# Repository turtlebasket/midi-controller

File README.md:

# Pocket Operator

## Contents

- [`device`](device/) - Board design files ([see README](device/README.md))
- [`firmware`](firmware/) - Device firmware ([see README](firmware/README.md))

## Gallery

| Completed Board (bird's eye) | Completed Board (top) |
| --------------- | -------- |
|  |  | 

| Layout (Top) | Layout (Bottom) | Layout (Full) |
| ------------ | --------------- | ------------- |
|  |  |  |

| Schematic |
| --------- |

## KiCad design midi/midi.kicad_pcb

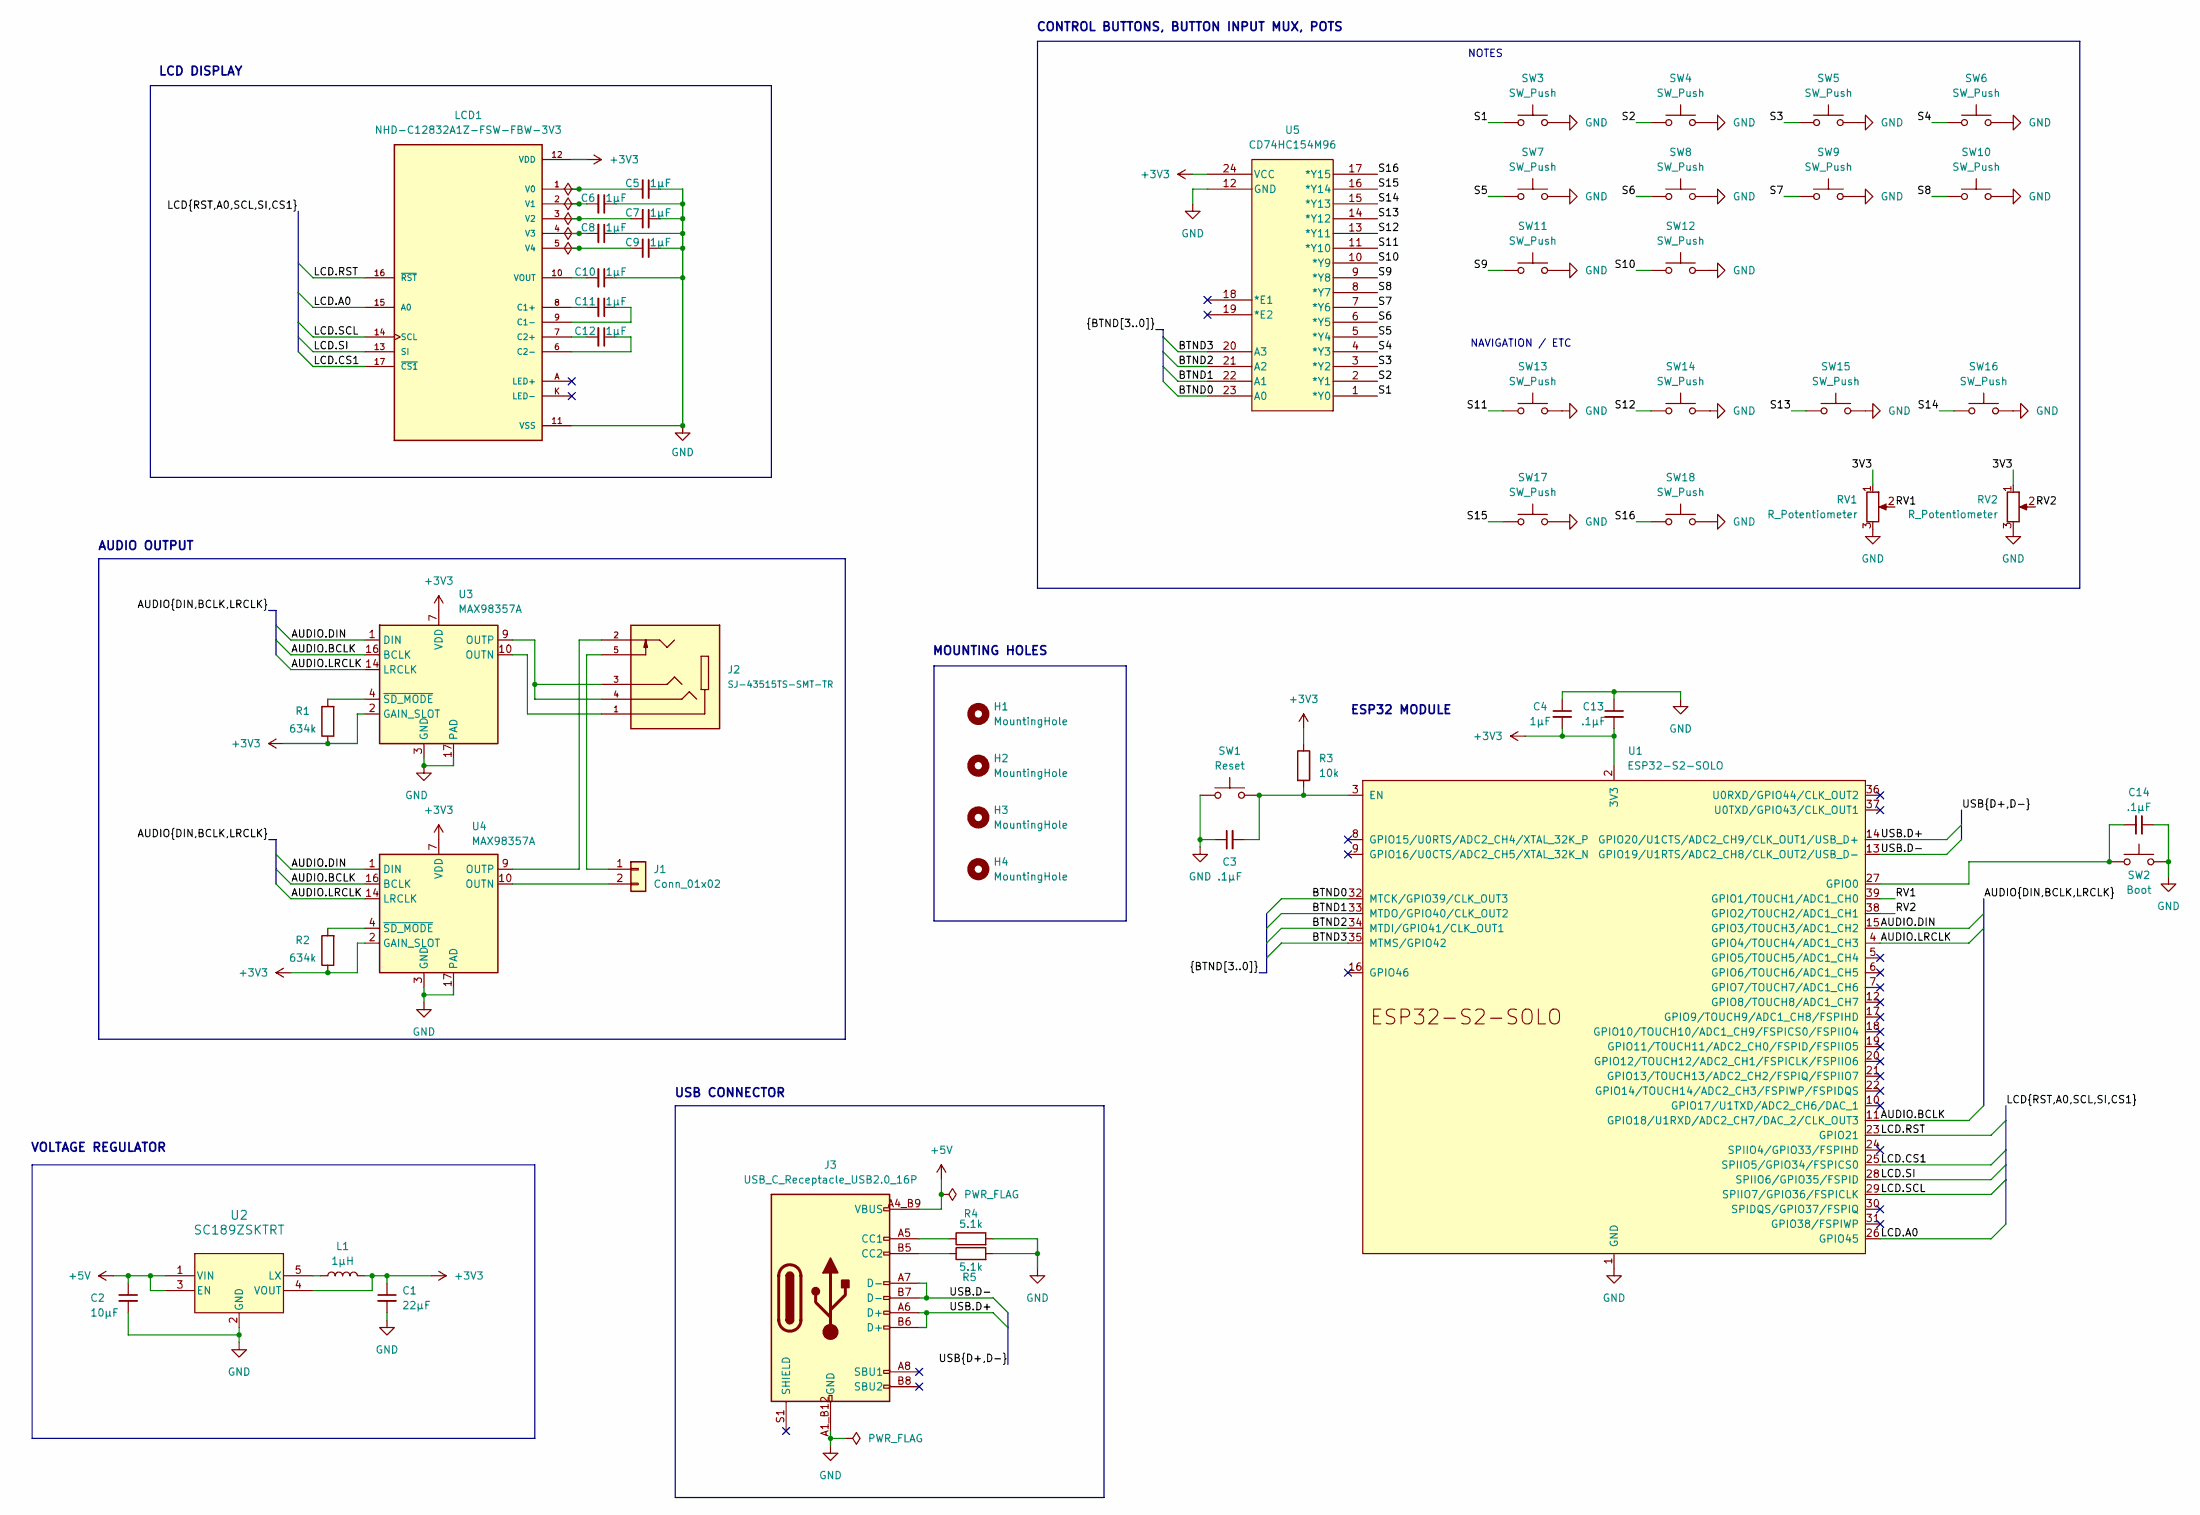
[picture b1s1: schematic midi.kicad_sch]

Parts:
C1: 22µF; C_0603_1608Metric_Pad1.08x0.95mm_HandSolder
C2: 10µF; C_0603_1608Metric_Pad1.08x0.95mm_HandSolder
C3, C13, C14: .1µF; C_0603_1608Metric_Pad1.08x0.95mm_HandSolder
C4: 1µF; C_0603_1608Metric_Pad1.08x0.95mm_HandSolder
C5, C6, C7, C8, C9, C10, C11, C12: 1µF; C_0603_1608Metric
H1, H2, H3, H4: MountingHole; MountingHole_2.2mm_M2
J1: Conn_01x02; PinHeader_1x02_P2.54mm_Vertical
J2: SJ-43515TS-SMT-TR; CUI_SJ-43515TS-SMT-TR; PARTREV 1.05
J3: USB_C_Receptacle_USB2.0_16P; GCT_USB4105-GF-A
L1: 1µH; L_0805_2012Metric_Pad1.15x1.40mm_HandSolder
LCD1: NHD-C12832A1Z-FSW-FBW-3V3; LCD_NHD-C12832A1Z-FSW-FBW-3V3; PARTREV 7
R1, R2: 634k; R_0603_1608Metric_Pad0.98x0.95mm_HandSolder
R3: 10k; R_0603_1608Metric_Pad0.98x0.95mm_HandSolder
R4, R5: 5.1k; R_0805_2012Metric_Pad1.20x1.40mm_HandSolder
RV1, RV2: R_Potentiometer; POT_PRS11R-4-S_BRN
SW1: Reset; SW_PUSH_6mm_H5mm
SW2: Boot; SW_PUSH_6mm_H5mm
SW3, SW4, SW5, SW6, SW7, SW8, SW9, SW10, SW11, SW12, SW13, SW14, SW15, SW16, SW17, SW18: SW_Push; SW_PUSH_6mm_H5mm
U1: ESP32-S2-SOLO
U2: SC189ZSKTRT; SOT23-5-SC189_SEM
U3, U4: MAX98357A; TQFN-16-1EP_3x3mm_P0.5mm_EP1.23x1.23mm
U5: CD74HC154M96; DW24

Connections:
+3V3: C1.1, C4.2, C13.2, L1.2, LCD1.12 (VDD), R1.1, R2.1, R3.1, U1.2 (3V3), U2.4 (VOUT), U3.2 (GAIN_SLOT), U3.7 (VDD), U3.8 (VDD), U4.2 (GAIN_SLOT), U4.7 (VDD), U4.8 (VDD), U5.24 (VCC)
+5V: C2.1, J3.A4_B9 (VBUS), J3.A9 (VBUS), J3.B4 (VBUS), J3.B9 (VBUS), U2.1 (VIN), U2.3 (EN)
/3V3: RV1.1, RV2.1
/AUDIO.BCLK: U1.11 (GPIO18/U1RXD/ADC2_CH7/DAC_2/CLK_OUT3), U3.16 (BCLK), U4.16 (BCLK)
/AUDIO.DIN: U1.15 (GPIO3/TOUCH3/ADC1_CH2), U3.1 (DIN), U4.1 (DIN)
/AUDIO.LRCLK: U1.4 (GPIO4/TOUCH4/ADC1_CH3), U3.14 (LRCLK), U4.14 (LRCLK)
/BTND0: U1.32 (MTCK/GPIO39/CLK_OUT3), U5.23 (A0)
/BTND1: U1.33 (MTDO/GPIO40/CLK_OUT2), U5.22 (A1)
/BTND2: U1.34 (MTDI/GPIO41/CLK_OUT1), U5.21 (A2)
/BTND3: U1.35 (MTMS/GPIO42), U5.20 (A3)
/LCD.A0: LCD1.15 (A0), U1.26 (GPIO45)
/LCD.CS1: LCD1.17 (~CS1), U1.25 (SPIIO5/GPIO34/FSPICS0)
/LCD.RST: LCD1.16 (~RST), U1.23 (GPIO21)
/LCD.SCL: LCD1.14 (SCL), U1.29 (SPIIO7/GPIO36/FSPICLK)
/LCD.SI: LCD1.13 (SI), U1.28 (SPIIO6/GPIO35/FSPID)
/RV1: RV1.2, U1.39 (GPIO1/TOUCH1/ADC1_CH0)
/RV2: RV2.2, U1.38 (GPIO2/TOUCH2/ADC1_CH1)
/S1: SW3.1, U5.1 (*Y0)
/S2: SW4.1, U5.2 (*Y1)
/S3: SW5.1, U5.3 (*Y2)
/S4: SW6.1, U5.4 (*Y3)
/S5: SW7.1, U5.5 (*Y4)
/S6: SW8.1, U5.6 (*Y5)
/S7: SW9.1, U5.7 (*Y6)
/S8: SW10.1, U5.8 (*Y7)
/S9: SW11.1, U5.9 (*Y8)
/S10: SW12.1, U5.10 (*Y9)
/S11: SW13.1, U5.11 (*Y10)
/S12: SW14.1, U5.13 (*Y11)
/S13: SW15.1, U5.14 (*Y12)
/S14: SW16.1, U5.15 (*Y13)
/S15: SW17.1, U5.16 (*Y14)
/S16: SW18.1, U5.17 (*Y15)
/USB.D+: J3.A6 (D+), J3.B6 (D+), U1.14 (GPIO20/U1CTS/ADC2_CH9/CLK_OUT1/USB_D+)
/USB.D-: J3.A7 (D-), J3.B7 (D-), U1.13 (GPIO19/U1RTS/ADC2_CH8/CLK_OUT2/USB_D-)
GND: C1.2, C2.2, C3.1, C4.1, C5.1, C6.1, C7.1, C8.1, C9.1, C10.1, C13.1, C14.1, J3.A1_B12 (GND), J3.A12 (GND), J3.B1 (GND), J3.B12 (GND), LCD1.11 (VSS), R4.2, R5.2, RV1.3, RV2.3, SW1.1, SW2.2, SW3.2, SW4.2, SW5.2, SW6.2, SW7.2, SW8.2, SW9.2, SW10.2, SW11.2, SW12.2, SW13.2, SW14.2, SW15.2, SW16.2, SW17.2, SW18.2, U1.1 (GND), U1.40 (GND), U1.41 (GND), U2.2 (GND), U3.3 (GND), U3.11 (GND), U3.15 (GND), U3.17 (PAD), U4.3 (GND), U4.11 (GND), U4.15 (GND), U4.17 (PAD), U5.12 (GND)
unnamed: J1.1, J2.5
unnamed: J1.2, U4.10 (OUTN)
unnamed: J3.A5 (CC1), R4.1
unnamed: J3.B5 (CC2), R5.1
unnamed: C11.2, LCD1.8 (C1+)
unnamed: C11.1, LCD1.9 (C1-)
unnamed: C12.2, LCD1.7 (C2+)
unnamed: C12.1, LCD1.6 (C2-)
unnamed: C5.2, LCD1.1 (V0)
unnamed: C6.2, LCD1.2 (V1)
unnamed: C7.2, LCD1.3 (V2)
unnamed: C8.2, LCD1.4 (V3)
unnamed: C9.2, LCD1.5 (V4)
unnamed: C10.2, LCD1.10 (VOUT)
unnamed: C3.2, R3.2, SW1.2, U1.3 (EN)
unnamed: C14.2, SW2.1, U1.27 (GPIO0)
unnamed: L1.1, U2.5 (LX)
unnamed: J2.1, U3.10 (OUTN)
unnamed: J2.3, J2.4, U3.9 (OUTP)
unnamed: R1.2, U3.4 (~SD_MODE)
unnamed: J2.2, U4.9 (OUTP)
unnamed: R2.2, U4.4 (~SD_MODE)

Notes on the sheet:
VOLTAGE REGULATOR
CONTROL BUTTONS, BUTTON INPUT MUX, POTS
AUDIO OUTPUT
MOUNTING HOLES
USB CONNECTOR
NOTES
ESP32 MODULE
NAVIGATION / ETC
LCD DISPLAY

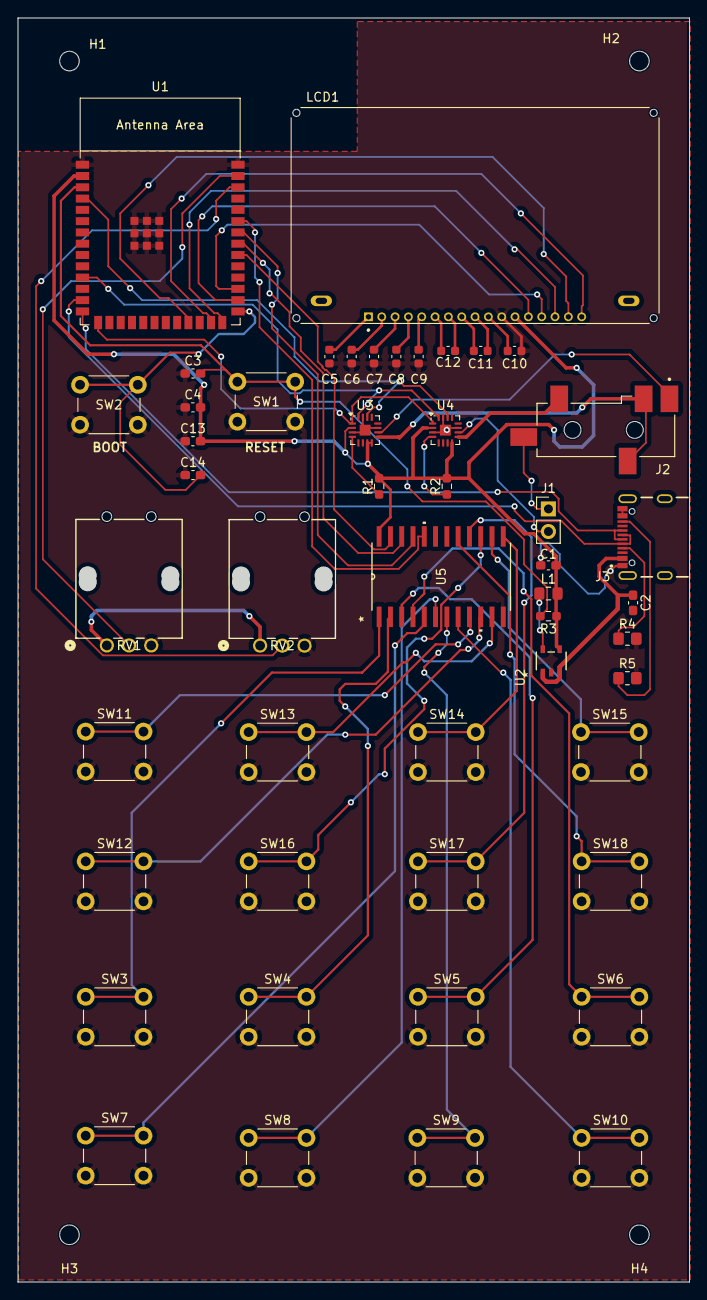
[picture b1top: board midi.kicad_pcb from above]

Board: 2 copper layers, 75.6 x 142.2 mm, 53 parts (0 on the bottom side), 58 nets.

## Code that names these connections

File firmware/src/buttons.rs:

use esp_idf_hal::{gpio::*, io::Error, peripherals::Peripherals, sys::EspError};

pub fn init_buttons() -> Result<[PinDriver<'static, AnyInputPin, Pull>; 4], EspError> {
    let peripherals = match Peripherals::take() {
        Ok(p) => p,
        Err(e) => return Err(e),
    };

    // wired to GPIO0, GPIO1, GPIO2, GPIO3
    let mut mux_bits = [
        (match PinDriver::input(peripherals.pins.gpio0) {
            Ok(b) => b,
            Err(e) => return Err(e),
        }),
        (match PinDriver::input(peripherals.pins.gpio1) {
            Ok(b) => b,
            Err(e) => return Err(e),
        }),
        (match PinDriver::input(peripherals.pins.gpio2) {
            Ok(b) => b,
            Err(e) => return Err(e),
        }),
        (match PinDriver::input(peripherals.pins.gpio3) {
            Ok(b) => b,
            Err(e) => return Err(e),
        }),
    ];

    for mux_bit in mux_bits.iter_mut() {
        mux_bit.set_pull(Pull::Up);
    }

    Ok(mux_bits)
}

/// decode the number of the button being pressed from 16-way (4-bit) multiplexer output
pub fn decode_button_number(bits: &[bool; 4]) -> u8 {
    let mut button_number = 0;
    for (i, bit) in bits.iter().enumerate() {
        if *bit {
            button_number |= 1 << i;
        }
    }
    button_number
}

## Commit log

2024-10-18 initialize
2024-10-18 add kicad ignores
2024-10-18 fix readme
2024-10-18 move kicad ignore / ignore backups
2024-10-18 remove midi/midi.kicad_prl
2024-10-18 add parts
2024-10-18 update esp32 from s2 to s3
2024-10-18 clean up pushbtn symbol
2024-10-18 use esp32-s3-wroom
2024-10-18 clean up pot, max98357A, USB-C port
2024-10-18 button/potentiometer layout
2024-10-18 add vreg schematic symbol
2024-10-19 added LTC1624 symbol, button layout, working on voltage reg
2024-10-19 finished voltage regulator
2024-10-19 page size increase and loaded screen
2024-10-20 schematic: link up audio i2s & LCD SPI bus
2024-10-21 add button input mux
2024-10-21 remove old voltage regulator
2024-10-30 added footprints for caps and some others
2024-10-30 downloaded mosfet footprint, tried to import footprint libs but failed
2024-10-30 downloaded L1 footprint
2024-10-30 can't get footprint import to work
2024-10-30 unfuck footprint assignments / significant progress on layout
2024-10-30 switch esp32 from s3 to s2 / use esplib, use USBC data connector, other tweaks
2024-10-31 wip: switch from LTC1624 to other vreg
2024-10-31 new vreg
2024-10-31 assign more footprints
2024-11-02 layout progress
2024-11-03 fix some layout issues
2024-11-05 slight ERC fixes for gnd/power in
2024-11-07 fix all ERC issues
2024-11-07 move power flag
2024-11-07 fixed ~60 clearance errors around LCD area
2024-11-08 more DRC fixes
2024-11-08 add mounting holes, slight fixes, redo pours
2024-11-08 close to finished
2024-11-09 rename pcb project
2024-11-09 add some assets
2024-11-09 start scaffold
2024-11-09 build changes
2024-11-10 scaffold from esp-idf-template
2024-11-10 scaffold project
2024-11-11 half-baked stuff
    from https://github.com/esp-rs/esp-idf-hal/tree/master/examples
2024-11-11 misc updates
2024-12-14 update gallery
2024-12-14 misc fw changes
